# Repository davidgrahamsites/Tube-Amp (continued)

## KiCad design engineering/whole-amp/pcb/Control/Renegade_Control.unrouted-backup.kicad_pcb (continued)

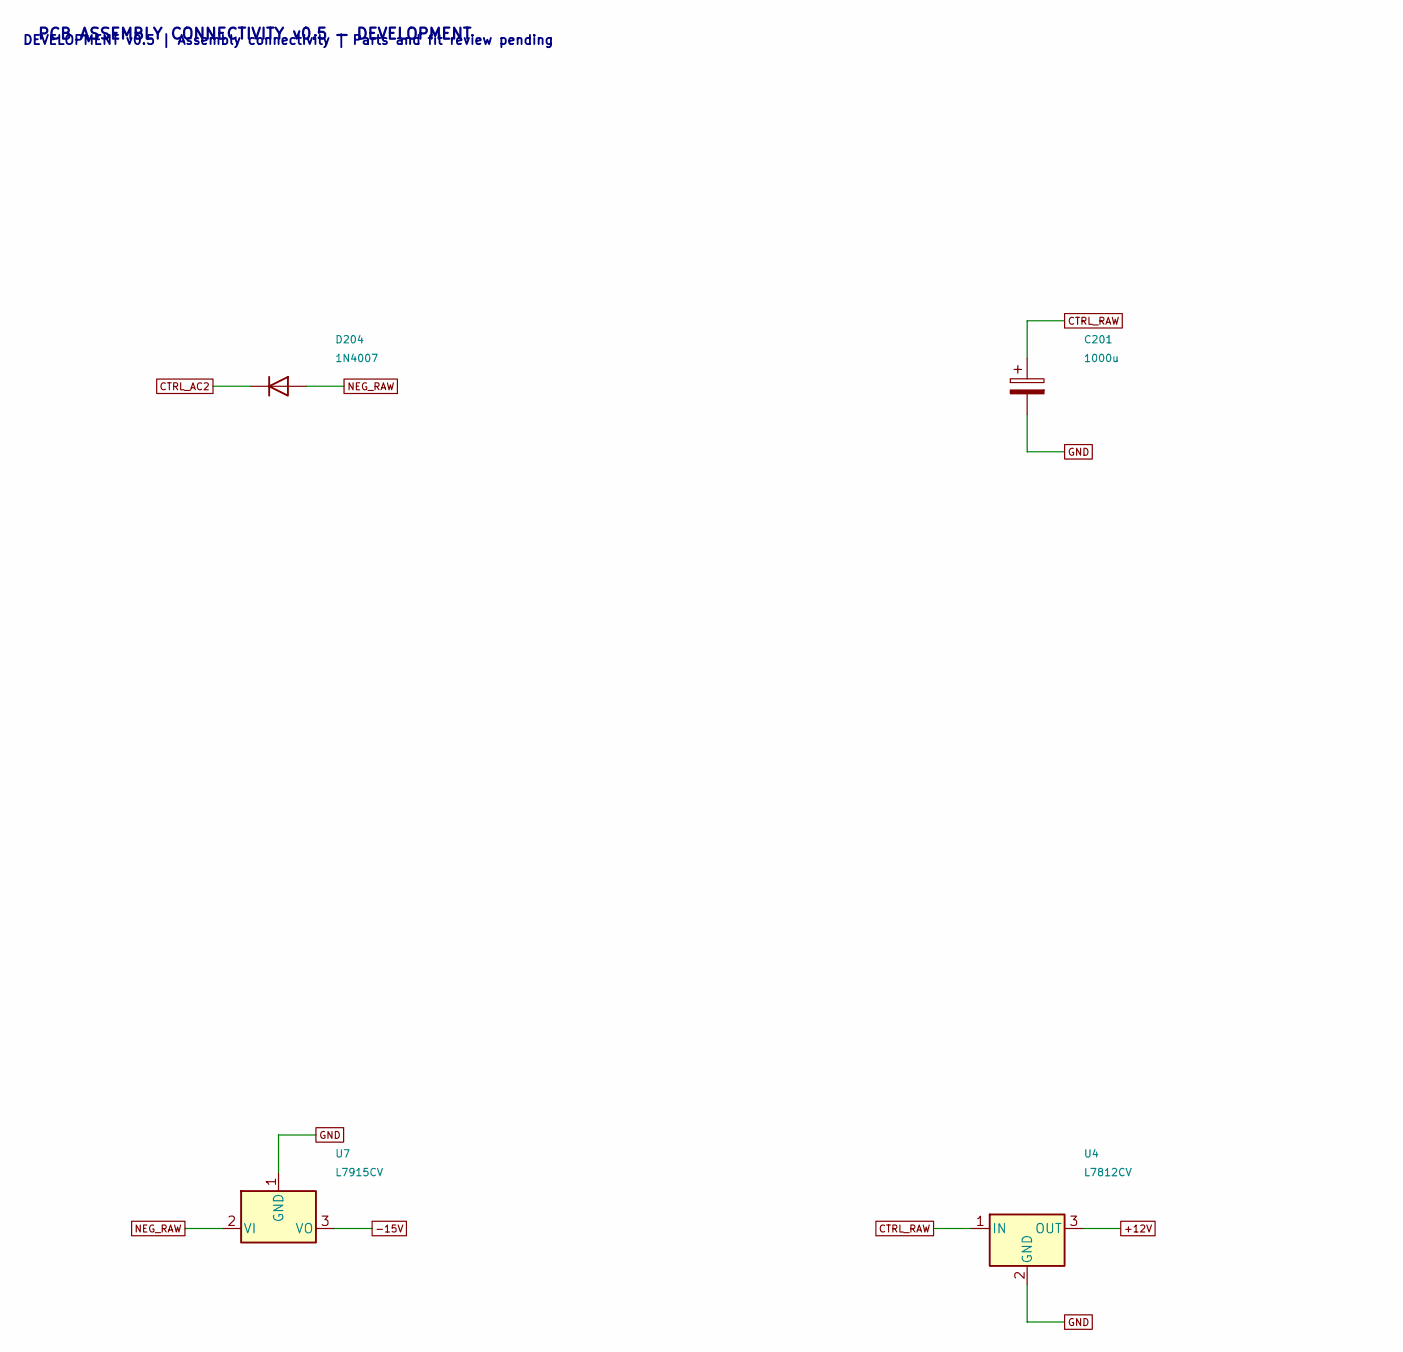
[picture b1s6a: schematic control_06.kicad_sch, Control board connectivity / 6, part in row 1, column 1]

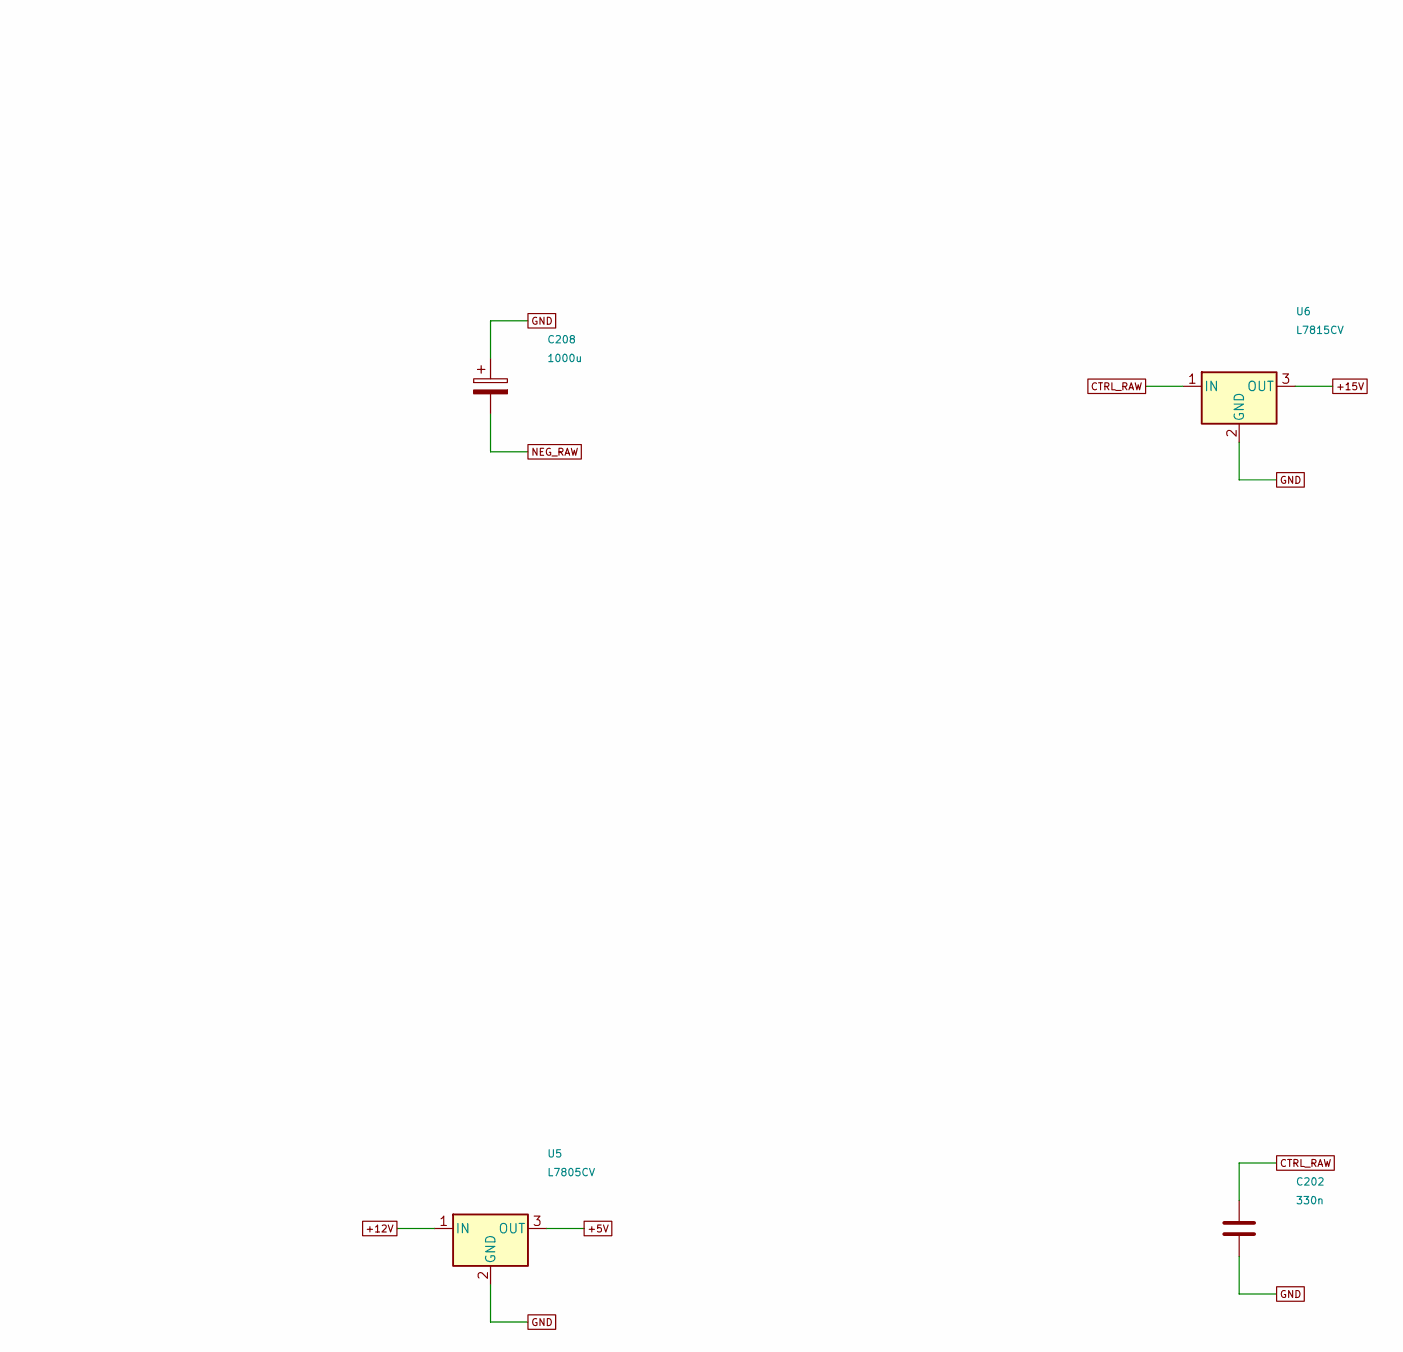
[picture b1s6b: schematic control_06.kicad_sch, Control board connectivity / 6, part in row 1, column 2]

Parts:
C201, C208: 1000u; CP_Radial_D16.0mm_P7.50mm; Rating 50V electrolytic, ripple rating required
C202: 330n; C_Rect_L7.2mm_W3.5mm_P5.00mm; Rating 63V film/C0G
D204: 1N4007; D_DO-41_SOD81_P10.16mm_Horizontal
U4: L7812CV; TO-220-3_Vertical; Rating TO220 heatsink; worst-case dissipation 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
U5: L7805CV; TO-220-3_Vertical
U6: L7815CV; TO-220-3_Vertical; Rating TO220 heatsink; ST datasheet
U7: L7915CV; TO-220-3_Vertical; Rating TO220 tab=negative input; isolated heat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

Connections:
+5V: U5.3 (OUT); also elsewhere on the board
+12V: U4.3 (OUT), U5.1 (IN); also elsewhere on the board
+15V: U6.3 (OUT); also elsewhere on the board
-15V: U7.3 (VO); also elsewhere on the board
CTRL_AC2: D204.1 (K); also elsewhere on the board
CTRL_RAW: C201.1, C202.1, U4.1 (IN), U6.1 (IN); also elsewhere on the board
GND: C201.2, C202.2, C208.1, U4.2 (GND), U5.2 (GND), U6.2 (GND), U7.1 (GND); also elsewhere on the board
NEG_RAW: C208.2, D204.2 (A), U7.2 (VI); also elsewhere on the board

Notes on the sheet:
PCB ASSEMBLY CONNECTIVITY v0.5 — DEVELOPMENT
DEVELOPMENT v0.5 | Assembly connectivity | Parts and fit review pending

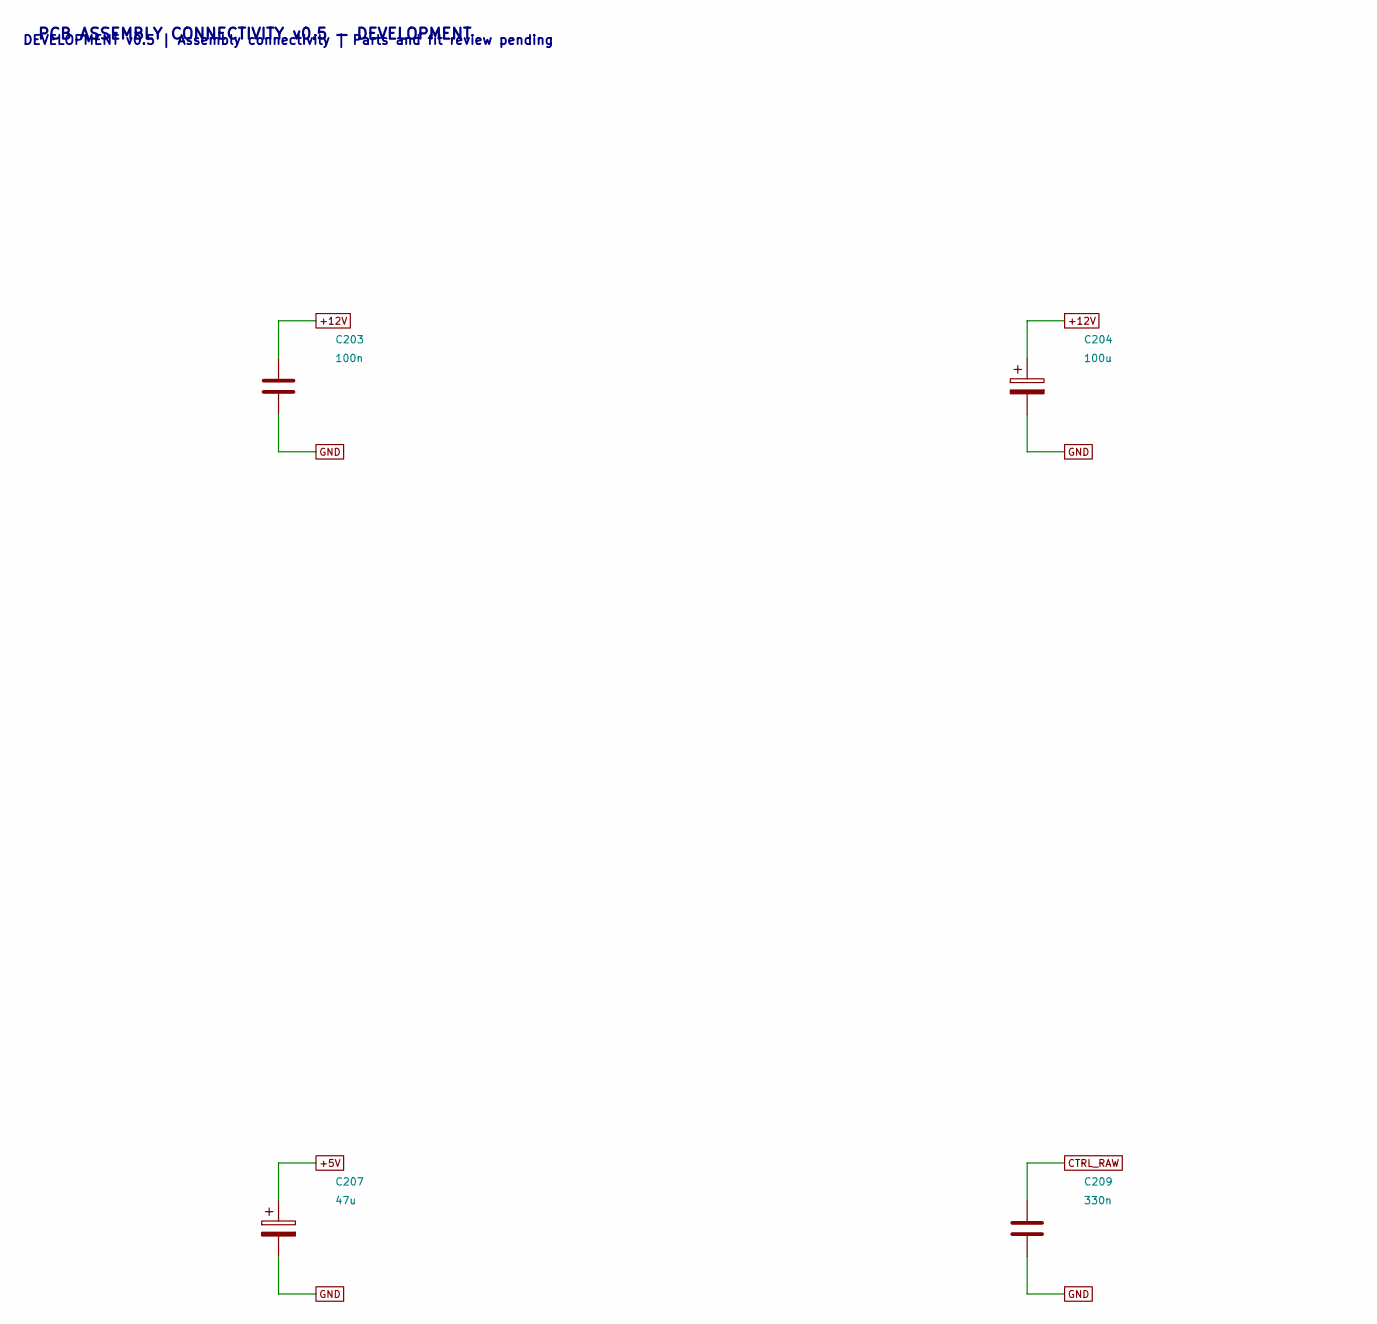
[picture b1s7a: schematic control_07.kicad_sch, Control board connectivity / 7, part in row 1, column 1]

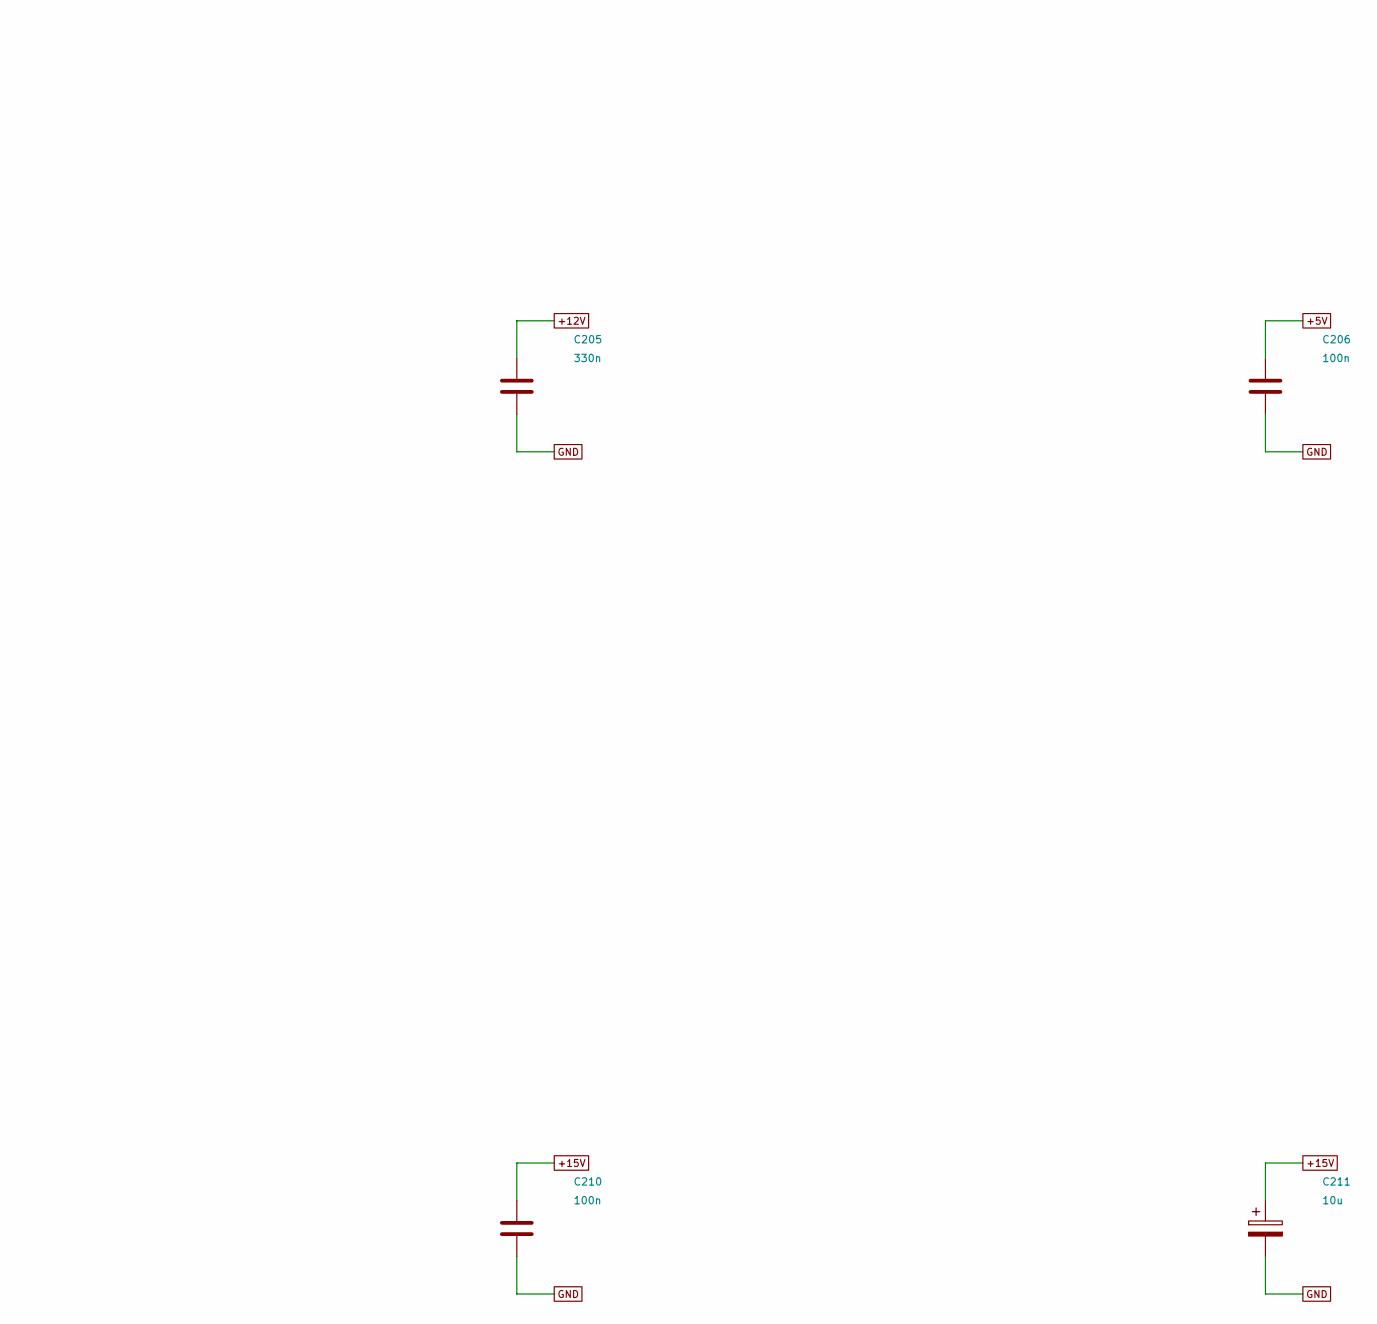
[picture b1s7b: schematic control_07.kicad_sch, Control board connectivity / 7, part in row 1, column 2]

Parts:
C203, C206, C210: 100n; C_Rect_L7.2mm_W3.5mm_P5.00mm; Rating 63V film/C0G
C204: 100u; CP_Radial_D8.0mm_P3.50mm; Rating 50V electrolytic
C205, C209: 330n; C_Rect_L7.2mm_W3.5mm_P5.00mm; Rating 63V film/C0G
C207: 47u; CP_Radial_D8.0mm_P3.50mm; Rating 50V electrolytic
C211: 10u; CP_Radial_D8.0mm_P3.50mm; Rating 50V electrolytic

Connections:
+5V: C206.1, C207.1; also elsewhere on the board
+12V: C203.1, C204.1, C205.1; also elsewhere on the board
+15V: C210.1, C211.1; also elsewhere on the board
CTRL_RAW: C209.1; also elsewhere on the board
GND: C203.2, C204.2, C205.2, C206.2, C207.2, C209.2, C210.2, C211.2; also elsewhere on the board

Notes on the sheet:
PCB ASSEMBLY CONNECTIVITY v0.5 — DEVELOPMENT
DEVELOPMENT v0.5 | Assembly connectivity | Parts and fit review pending

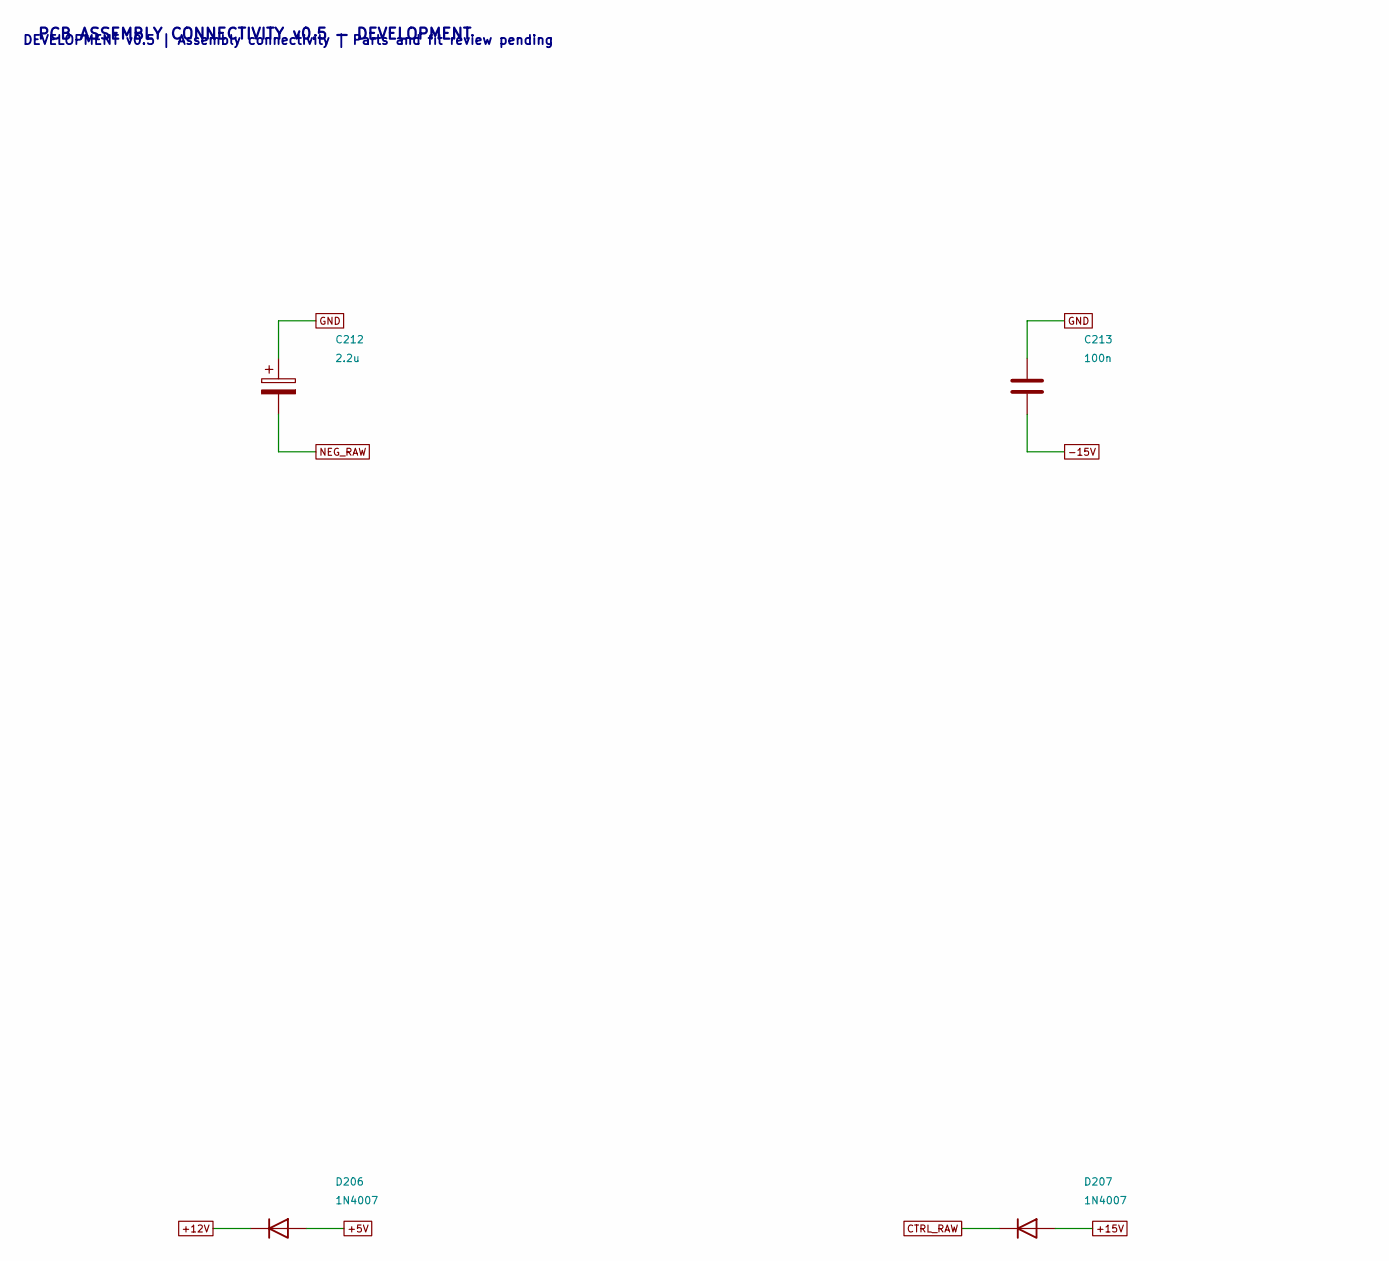
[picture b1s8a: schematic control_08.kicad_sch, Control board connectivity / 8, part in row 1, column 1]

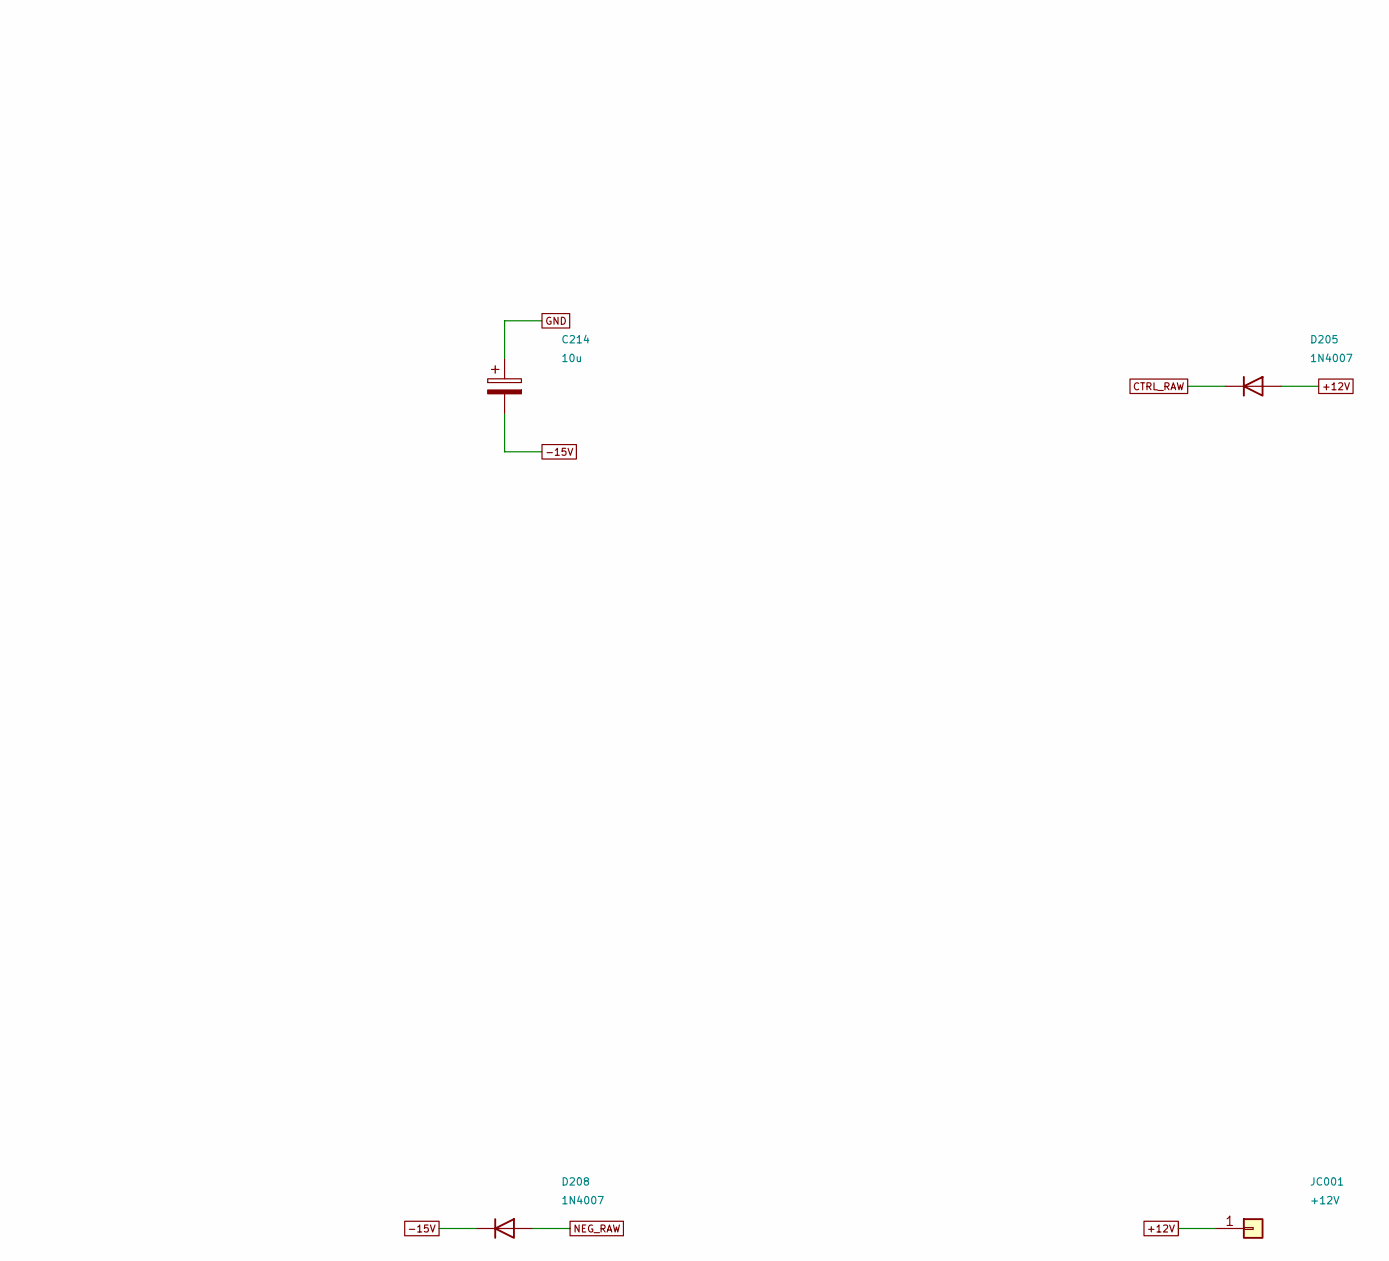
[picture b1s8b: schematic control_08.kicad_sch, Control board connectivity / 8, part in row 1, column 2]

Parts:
C212: 2.2u; CP_Radial_D8.0mm_P3.50mm; Rating 50V electrolytic
C213: 100n; C_Rect_L7.2mm_W3.5mm_P5.00mm; Rating 63V film/C0G
C214: 10u; CP_Radial_D8.0mm_P3.50mm; Rating 50V electrolytic
D205, D206, D207, D208: 1N4007; D_DO-41_SOD81_P10.16mm_Horizontal
JC001: +12V; WirePad_1.3mm; Rating Soldered and strain-relieved wire, volt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

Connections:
+5V: D206.2 (A); also elsewhere on the board
+12V: D205.2 (A), D206.1 (K), JC001.1; also elsewhere on the board
+15V: D207.2 (A); also elsewhere on the board
-15V: C213.2, C214.2, D208.1 (K); also elsewhere on the board
CTRL_RAW: D205.1 (K), D207.1 (K); also elsewhere on the board
GND: C212.1, C213.1, C214.1; also elsewhere on the board
NEG_RAW: C212.2, D208.2 (A); also elsewhere on the board

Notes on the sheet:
PCB ASSEMBLY CONNECTIVITY v0.5 — DEVELOPMENT
DEVELOPMENT v0.5 | Assembly connectivity | Parts and fit review pending

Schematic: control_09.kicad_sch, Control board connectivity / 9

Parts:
JC002: +15V; WirePad_1.3mm; Rating Soldered and strain-relieved wire, volt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
JC003: -15V; WirePad_1.3mm; Rating Soldered and strain-relieved wire, volt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
JC004: BTN_CH; WirePad_1.3mm; Rating Soldered and strain-relieved wire, volt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
JC005: BTN_REV; WirePad_1.3mm; Rating Soldered and strain-relieved wire, volt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
JC006: COIL_CH; WirePad_1.3mm; Rating Soldered and strain-relieved wire, volt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
JC007: COIL_REV; WirePad_1.3mm; Rating Soldered and strain-relieved wire, volt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
JC008: CTRL_AC1; WirePad_1.3mm; Rating Soldered and strain-relieved wire, volt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
JC009: CTRL_AC2; WirePad_1.3mm; Rating Soldered and strain-relieved wire, volt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

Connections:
+15V: JC002.1; also elsewhere on the board
-15V: JC003.1; also elsewhere on the board
BTN_CH: JC004.1; also elsewhere on the board
BTN_REV: JC005.1; also elsewhere on the board
COIL_CH: JC006.1; also elsewhere on the board
COIL_REV: JC007.1; also elsewhere on the board
CTRL_AC1: JC008.1; also elsewhere on the board
CTRL_AC2: JC009.1; also elsewhere on the board

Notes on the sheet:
PCB ASSEMBLY CONNECTIVITY v0.5 — DEVELOPMENT
DEVELOPMENT v0.5 | Assembly connectivity | Parts and fit review pending

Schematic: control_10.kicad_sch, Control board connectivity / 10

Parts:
H1, H2, H3, H4: MountingHole_3.2mm_M3
JC010: GND; WirePad_1.3mm; Rating Soldered and strain-relieved wire, volt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
JC011: MR_N; WirePad_1.3mm; Rating Soldered and strain-relieved wire, volt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
JC012: PEDAL_CH; WirePad_1.3mm; Rating Soldered and strain-relieved wire, volt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
JC013: PEDAL_REV; WirePad_1.3mm; Rating Soldered and strain-relieved wire, volt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

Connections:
GND: JC010.1; also elsewhere on the board
MR_N: JC011.1; also elsewhere on the board
PEDAL_CH: JC012.1; also elsewhere on the board
PEDAL_REV: JC013.1; also elsewhere on the board

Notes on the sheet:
PCB ASSEMBLY CONNECTIVITY v0.5 — DEVELOPMENT
DEVELOPMENT v0.5 | Assembly connectivity | Parts and fit review pending

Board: 2 copper layers, 72 parts (0 on the bottom side), 28 nets, no tracks yet.

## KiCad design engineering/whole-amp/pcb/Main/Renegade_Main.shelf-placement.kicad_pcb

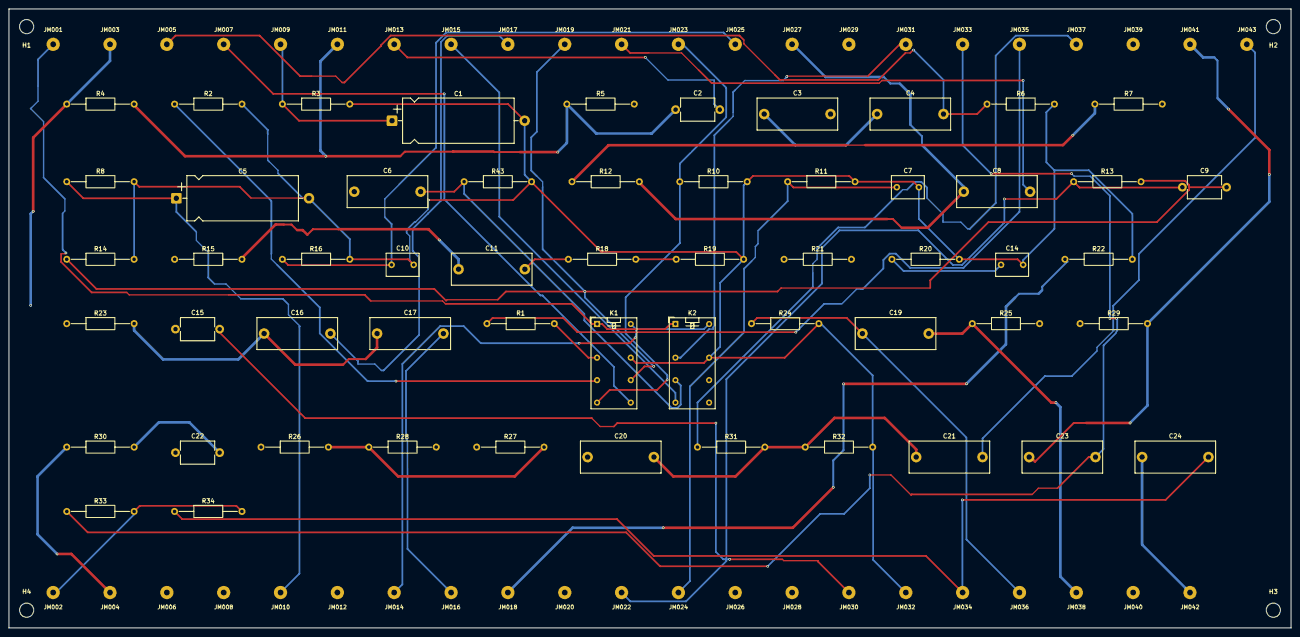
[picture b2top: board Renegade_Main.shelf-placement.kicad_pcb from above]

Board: 2 copper layers, 290.0 x 140.0 mm, 103 parts (0 on the bottom side), 50 nets.

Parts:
C1, C5: 25u; CP_Axial_L25.0mm_D10.0mm_P30.00mm_Horizontal
C2: 250p; C_Disc_D7.5mm_W5.0mm_P10.00mm
C3, C20, C21: 100n; C_Rect_L18.0mm_W7.0mm_P15.00mm_FKS3_FKP3
C4, C6: 47n; C_Rect_L18.0mm_W7.0mm_P15.00mm_FKS3_FKP3
C7: 680n; C_Rect_L7.2mm_W5.0mm_P5.00mm
C8, C11, C16, C17, C19, C23, C24: 22n; C_Rect_L18.0mm_W7.0mm_P15.00mm_FKS3_FKP3
C9, C15: 470p; C_Disc_D7.5mm_W5.0mm_P10.00mm
C10, C14: 1u; C_Rect_L7.2mm_W5.0mm_P5.00mm
C22: 47p; C_Disc_D7.5mm_W5.0mm_P10.00mm
H1, H2, H3, H4: MountingHole_3.2mm_M3
JM001: +12V; WirePad_1.3mm
JM002: BIAS_OUT; WirePad_1.3mm
JM003: B_EARLY; WirePad_1.3mm
JM004: B_PRE; WirePad_1.3mm
JM005: CL_BASS_BOTTOM; WirePad_1.3mm
JM006: CL_BASS_TOP; WirePad_1.3mm
JM007: CL_G2; WirePad_1.3mm
JM008: CL_IN; WirePad_1.3mm
JM009: CL_K1; WirePad_1.3mm
JM010: CL_K2; WirePad_1.3mm
JM011: CL_P1; WirePad_1.3mm
JM012: CL_P2; WirePad_1.3mm
JM013: CL_TREBLE_TOP; WirePad_1.3mm
JM014: COIL_CH; WirePad_1.3mm
JM015: DIRTY_OUT; WirePad_1.3mm
JM016: DR_BASS_BOTTOM; WirePad_1.3mm
JM017: DR_BASS_TOP; WirePad_1.3mm
JM018: DR_CF; WirePad_1.3mm
JM019: DR_G2; WirePad_1.3mm
JM020: DR_G3; WirePad_1.3mm
JM021: DR_GAIN_TOP; WirePad_1.3mm
JM022: DR_GAIN_W; WirePad_1.3mm
JM023: DR_IN; WirePad_1.3mm
JM024: DR_K1; WirePad_1.3mm
JM025: DR_K2; WirePad_1.3mm
JM026: DR_K3; WirePad_1.3mm
JM027: DR_P1; WirePad_1.3mm
JM028: DR_P2; WirePad_1.3mm
JM029: DR_P3; WirePad_1.3mm
JM030: DR_TREBLE_TOP; WirePad_1.3mm
JM031: FX_SEND; WirePad_1.3mm
JM032: GND; WirePad_1.3mm
JM033: GRID_A_FEED; WirePad_1.3mm
JM034: GRID_B_FEED; WirePad_1.3mm
JM035: INPUT; WirePad_1.3mm
JM036: MIX_OUT; WirePad_1.3mm
JM037: OT_4; WirePad_1.3mm
JM038: PI_G1; WirePad_1.3mm
JM039: PI_G2; WirePad_1.3mm
JM040: PI_K; WirePad_1.3mm
JM041: PI_P1; WirePad_1.3mm
JM042: PI_P2; WirePad_1.3mm
JM043: PRES_TOP; WirePad_1.3mm
K1, K2: G5V-2-H1 DC12 (candidate); Relay_DPDT_Omron_G5V-2
R1: 68k; R_Axial_DIN0207_L6.3mm_D2.5mm_P15.24mm_Horizontal
R2, R10, R25, R27: 1M; R_Axial_DIN0207_L6.3mm_D2.5mm_P15.24mm_Horizontal
R3, R8: 1.5k; R_Axial_DIN0207_L6.3mm_D2.5mm_P15.24mm_Horizontal
R4, R5, R7, R12, R15, R21, R22, R30, R31: 100k; R_Axial_DIN0207_L6.3mm_D2.5mm_P15.24mm_Horizontal
R6: 15k; R_Axial_DIN0207_L6.3mm_D2.5mm_P15.24mm_Horizontal
R11: 2.7k; R_Axial_DIN0207_L6.3mm_D2.5mm_P15.24mm_Horizontal
R13, R14, R18, R19: 470k; R_Axial_DIN0207_L6.3mm_D2.5mm_P15.24mm_Horizontal
R16: 1.8k; R_Axial_DIN0207_L6.3mm_D2.5mm_P15.24mm_Horizontal
R20: 820; R_Axial_DIN0207_L6.3mm_D2.5mm_P15.24mm_Horizontal
R23: 33k; R_Axial_DIN0207_L6.3mm_D2.5mm_P15.24mm_Horizontal
R24, R43: 10M; R_Axial_DIN0207_L6.3mm_D2.5mm_P15.24mm_Horizontal
R26: 470; R_Axial_DIN0207_L6.3mm_D2.5mm_P15.24mm_Horizontal
R28: 10k; R_Axial_DIN0207_L6.3mm_D2.5mm_P15.24mm_Horizontal
R29: 82k; R_Axial_DIN0207_L6.3mm_D2.5mm_P15.24mm_Horizontal
R32: 47k; R_Axial_DIN0207_L6.3mm_D2.5mm_P15.24mm_Horizontal
R33, R34: 220k; R_Axial_DIN0207_L6.3mm_D2.5mm_P15.24mm_Horizontal

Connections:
+12V: JM001.1, K1.1, K2.1
BIAS_OUT: JM002.1, R33.2, R34.2
B_EARLY: JM003.1, R4.1, R7.1, R12.1, R15.1
B_PRE: JM004.1, R21.1, R29.1, R30.1
CLEAN_OUT: C6.2, K2.6, R43.1
CL_BASS_BOTTOM: C4.2, JM005.1, R6.1
CL_BASS_TOP: C3.2, JM006.1
CL_G2: JM007.1, K1.9
CL_IN: JM008.1, K1.6, R2.1
CL_K1: C1.1, JM009.1, R3.1
CL_K2: C5.1, JM010.1, R8.1
CL_P1: C2.1, JM011.1, R4.2, R5.1
CL_P2: C6.1, JM012.1, R7.2
CL_TONE: C3.1, C4.1, R5.2
CL_TREBLE_TOP: C2.2, JM013.1
COIL_CH: JM014.1, K1.16, K2.16
DIRTY_OUT: JM015.1, K2.8
DR_BASS_BOTTOM: C17.2, JM016.1
DR_BASS_TOP: C16.2, JM017.1
DR_C3: C11.2, R18.1
DR_CF: C15.1, JM018.1, R22.1, R23.1
DR_G2: C9.2, JM019.1, K1.11, R13.2, R14.1
DR_G3: JM020.1, R18.2, R19.1
DR_GAIN_TOP: C8.2, JM021.1
DR_GAIN_W: C9.1, JM022.1, R13.1
DR_IN: JM023.1, K1.8, R10.1
DR_K1: C7.1, JM024.1, R11.1
DR_K2: C10.1, JM025.1, R16.1
DR_K3: C14.1, JM026.1, R20.1
DR_P1: C8.1, JM027.1, R12.2
DR_P2: C11.1, JM028.1, R15.2
DR_P3: JM029.1, R21.2
DR_TONE: C16.1, C17.1, R23.2
DR_TREBLE_TOP: C15.2, JM030.1
FX_SEND: JM031.1, K2.4
GND: C1.2, C5.2, C7.2, C10.2, C14.2, JM032.1, K1.13, K2.13, R2.2, R3.2, R6.2, R8.2, R10.2, R11.2, R14.2, R16.2, R19.2, R20.2, R22.2, R24.2, R32.2, R43.2
GRID_A_FEED: C23.2, JM033.1, R33.1
GRID_B_FEED: C24.2, JM034.1, R34.1
INPUT: JM035.1, R1.1
INPUT_STOP: K1.4, R1.2
MIX_OUT: C19.1, JM036.1, R24.1
NFB_NODE: C20.2, C21.1, R28.2, R31.2, R32.1
OT_4: JM037.1, R31.1
PI_G1: C19.2, JM038.1, R25.1
PI_G2: C20.1, JM039.1, R27.1
PI_K: JM040.1, R26.1
PI_P1: C22.1, C23.1, JM041.1, R29.2
PI_P2: C22.2, C24.1, JM042.1, R30.2
PI_TAIL_TOP: R25.2, R26.2, R27.2, R28.1
PRES_TOP: C21.2, JM043.1

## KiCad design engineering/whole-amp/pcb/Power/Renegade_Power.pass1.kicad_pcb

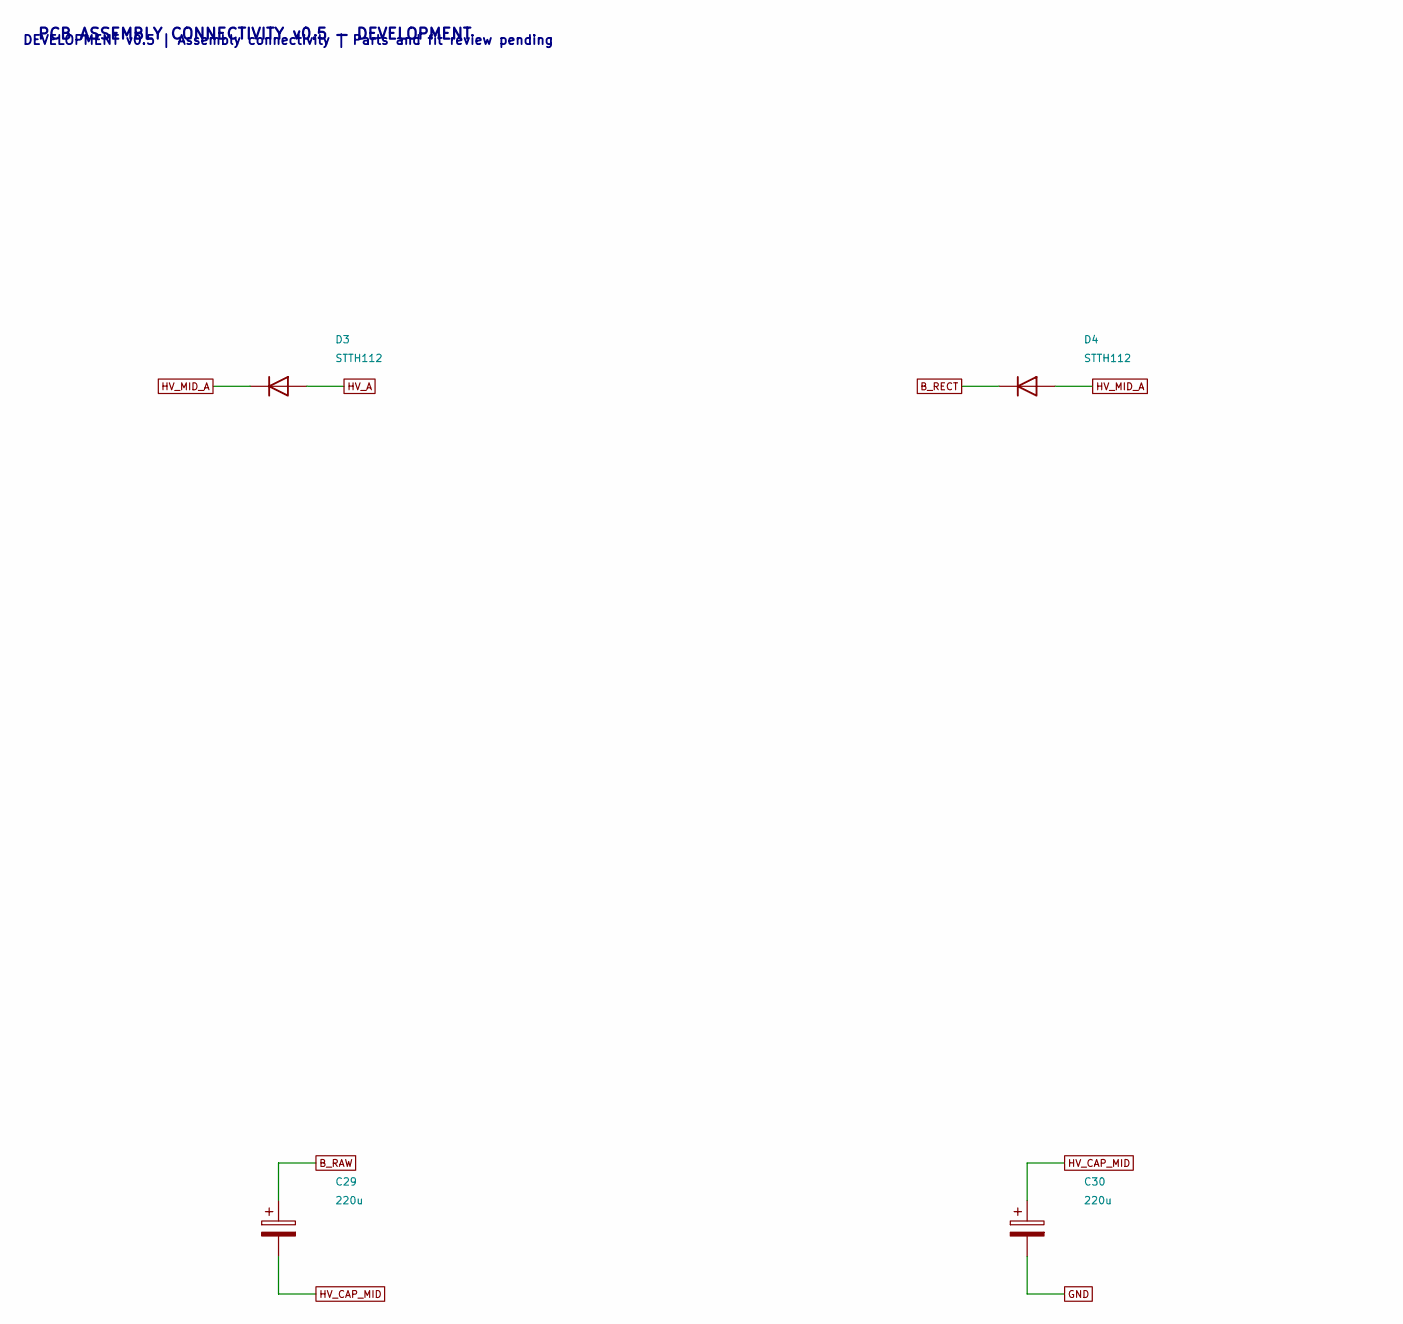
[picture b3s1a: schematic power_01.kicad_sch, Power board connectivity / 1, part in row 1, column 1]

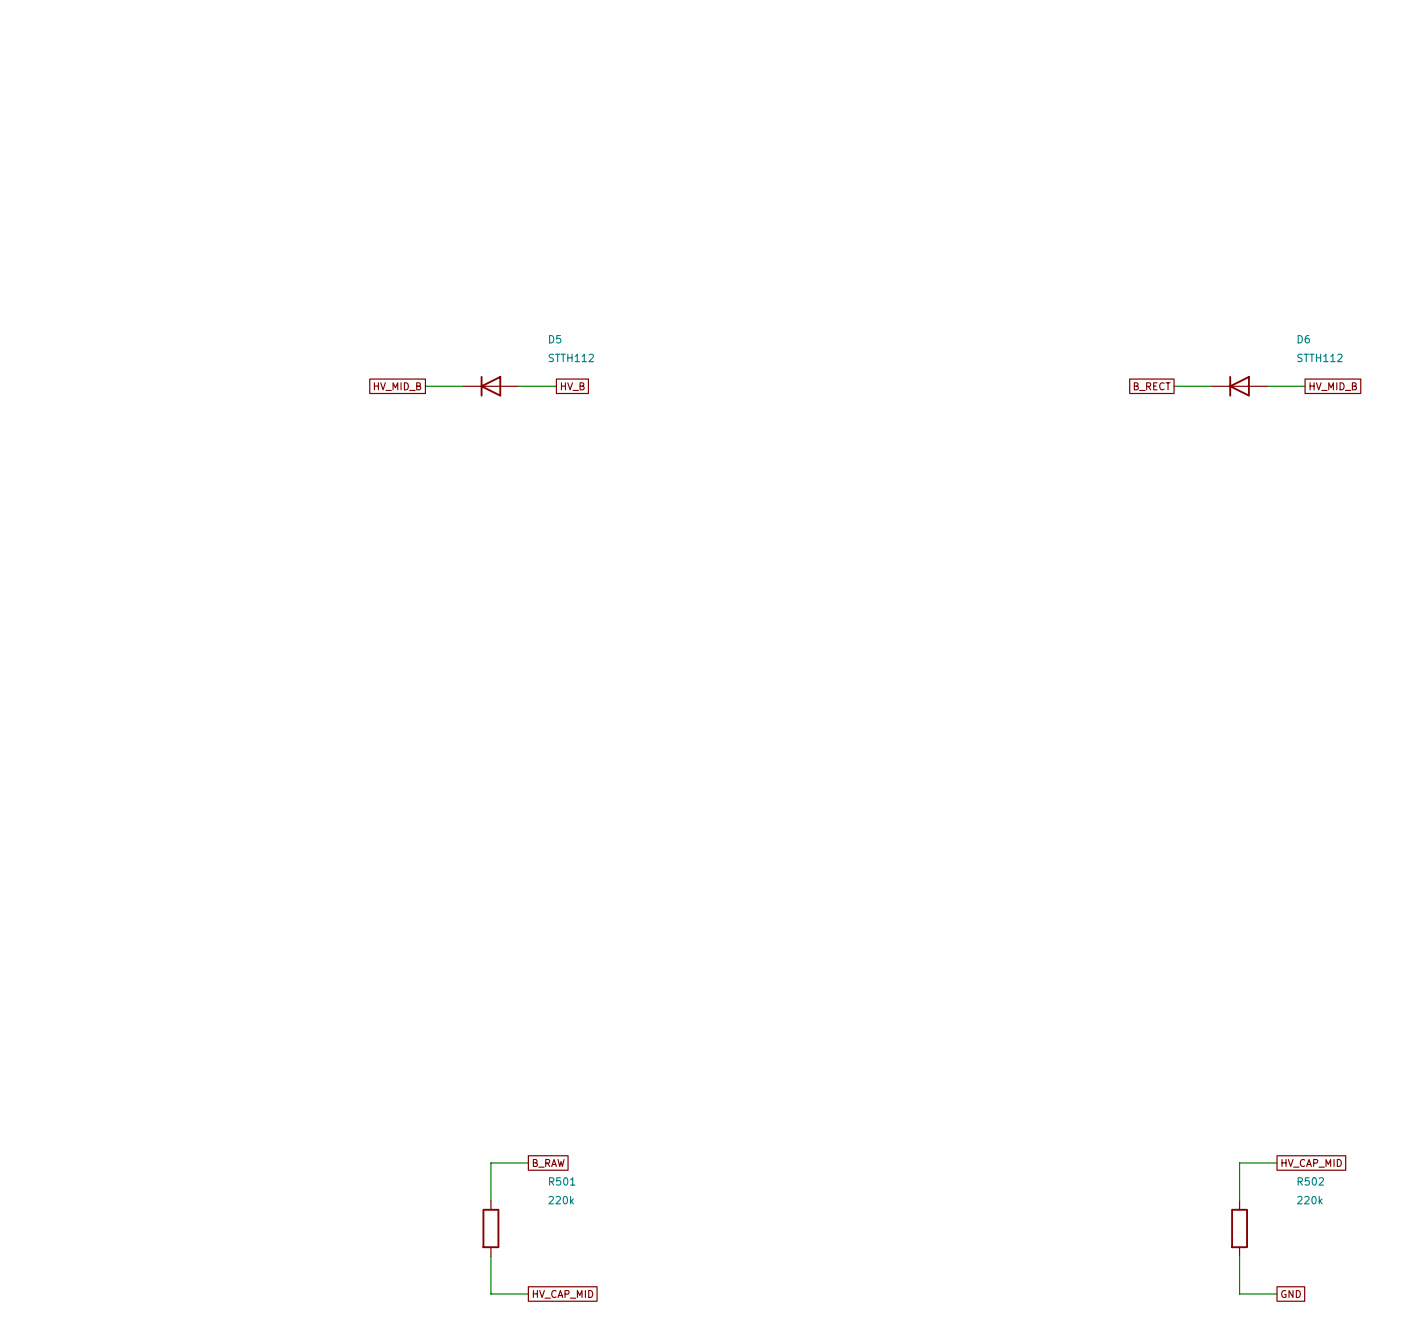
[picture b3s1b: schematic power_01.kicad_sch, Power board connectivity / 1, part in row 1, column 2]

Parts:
C29, C30: 220u; CP_Radial_D22.0mm_P10.00mm_SnapIn; Rating 220uF 400V; 22x30mm nominal, max23.5x32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
D3, D4, D5, D6: STTH112; D_DO-41_SOD81_P12.70mm_Horizontal; Rating 1200V 1A DO41; axial part, not STTH112A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
R501, R502: 220k; R_Axial_DIN0414_L11.9mm_D4.5mm_P15.24mm_Horizontal; Rating 2 W; 350 V working minimum

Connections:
B_RAW: C29.1, R501.1; also elsewhere on the board
B_RECT: D4.1 (K), D6.1 (K); also elsewhere on the board
GND: C30.2, R502.2; also elsewhere on the board
HV_A: D3.2 (A); also elsewhere on the board
HV_B: D5.2 (A); also elsewhere on the board
HV_CAP_MID: C29.2, C30.1, R501.2, R502.1
HV_MID_A: D3.1 (K), D4.2 (A)
HV_MID_B: D5.1 (K), D6.2 (A)

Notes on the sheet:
PCB ASSEMBLY CONNECTIVITY v0.5 — DEVELOPMENT
DEVELOPMENT v0.5 | Assembly connectivity | Parts and fit review pending
